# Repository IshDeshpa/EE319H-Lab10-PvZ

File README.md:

# EE319H-Lab10-PvZ
Luke Mason and Ishan Deshpande's EE319H Final Project: Plants vs Zombies

This is a close representation of the real PvZ mobile/console game.

# Game description:
A mob of fun-loving zombies is about to invade your home, and your only defense is an arsenal of 8 zombie-zapping plants. Use peashooters, wall-nuts, cherry bombs and more to mulchify 8 different types of zombies before they can reach your front door.

# Project notes:
The TM4C has 256kB of flash memory (read only for our purposes), and 32kB of SRAM. Additionally, the display, the ST7735R TFT LCD display, was 160x128p, and could support a microSD card of 4GB formatted in FAT16. 

The sprites and sound effects took up almost all 256kB flash, and the in game objects took up almost all of our 32kB SRAM. In total, there were almost 100 sprites, and 7 sound effects. Each plant and zombie had animations with up to 7 sprites. For sound, we used an 8-bit DAC, and the MC34119P amplifier chip, which was paired with a 1MOhm feedback potentiometer, and a high pass filter for sound smoothing.

We implemented the eight starter plants in the game: Sunflower, Peashooter, Potato Mine, Snow Pea, Repeater, Cherry Bomb, Chomper, and Wall-nut. We also implemented eight zombies: regular zombie, conehead, buckethead, polevault, newspaper, jack-in-the-box, football, and flag zombie.

Some of the biggest challenges we ran into involved unrendering the sprites so as to not cause sprite clipping or leftover sprite data upon death. We also had to rewrite the drivers for displaying sprites to be oriented in landscape form.

You can watch our video showcase for our class design competition here: https://www.youtube.com/watch?v=L5PAtDdpwP4
Our game ran rather well with high sprite counts. This can be seen in this additional video, for anyone interested: https://youtu.be/gowIHrNNptc 

Scrapped Features:
- We were intending to implement a VS mode, which was scrapped due to lack of time. 
- We were intending to have music play during the game. However, after extensive debugging of the provided sound drivers, as well as an attempted switch to DMA, we decided that it was not worth our time to combine the display with reading music off of the microSD (Long WAV files are too big to contain in our flash memory, so you have to read it from the display microSD, which detracts from our ability to write SPI to the display's screen)
- We were also intending to seat our diplay and controls on a PCB. Unfortunately, those were lost in delivery, so we threw together a cardboard game controller.

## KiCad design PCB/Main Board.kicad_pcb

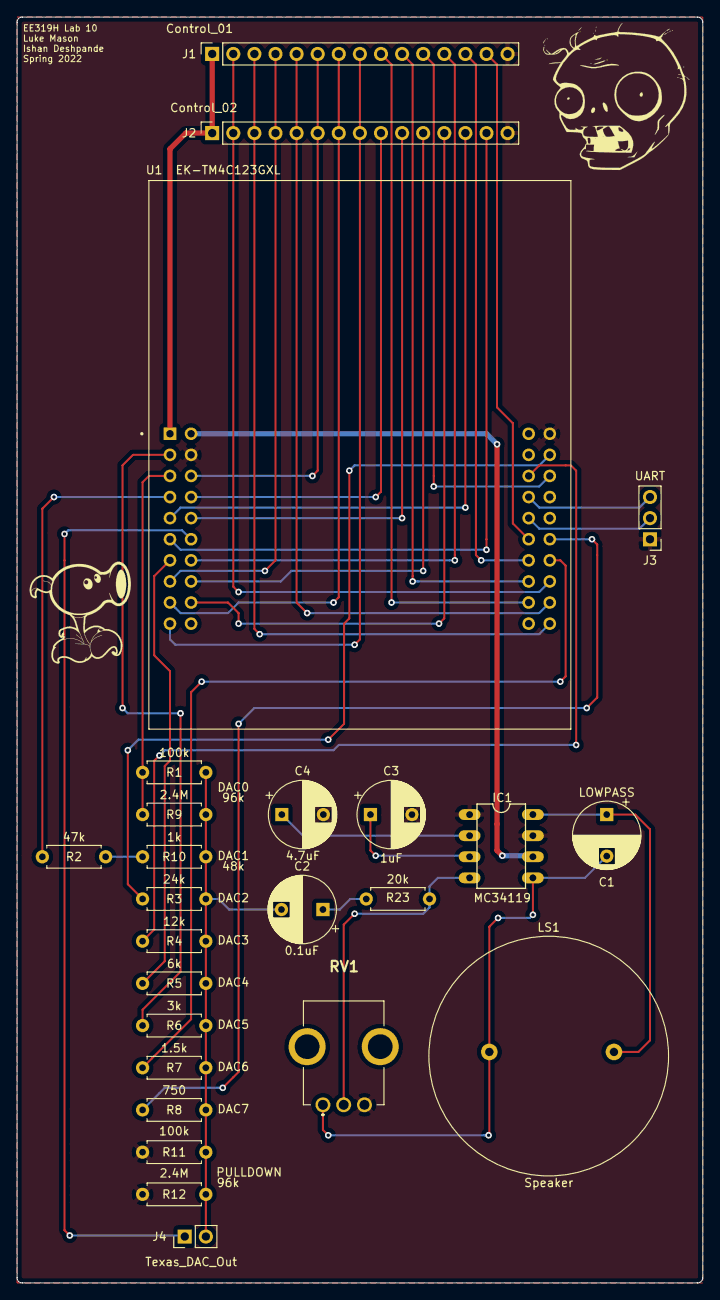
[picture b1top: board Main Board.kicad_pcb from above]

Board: 2 copper layers, 82.5 x 152.4 mm, 25 parts (0 on the bottom side), 41 nets.

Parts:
C1: LOWPASS; CP_Radial_D8.0mm_P5.00mm
C2: 0.1uF; CP_Radial_D8.0mm_P5.00mm
C3: 1uF; CP_Radial_D8.0mm_P5.00mm
C4: 4.7uF; CP_Radial_D8.0mm_P5.00mm
IC1: MC34119; DIL08
J1: Control_01; PinSocket_1x15_P2.54mm_Vertical
J2: Control_02; PinSocket_1x15_P2.54mm_Vertical
J3: UART; PinHeader_1x03_P2.54mm_Vertical
J4: Texas_DAC_Out; PinHeader_1x02_P2.54mm_Vertical
LS1: Speaker; AST-03008MR-R
R1, R11: 100k; R_Axial_DIN0207_L6.3mm_D2.5mm_P7.62mm_Horizontal
R2: 47k; R_Axial_DIN0207_L6.3mm_D2.5mm_P7.62mm_Horizontal
R3: 24k; R_Axial_DIN0207_L6.3mm_D2.5mm_P7.62mm_Horizontal
R4: 12k; R_Axial_DIN0207_L6.3mm_D2.5mm_P7.62mm_Horizontal
R5: 6k; R_Axial_DIN0207_L6.3mm_D2.5mm_P7.62mm_Horizontal
R6: 3k; R_Axial_DIN0207_L6.3mm_D2.5mm_P7.62mm_Horizontal
R7: 1.5k; R_Axial_DIN0207_L6.3mm_D2.5mm_P7.62mm_Horizontal
R8: 750; R_Axial_DIN0207_L6.3mm_D2.5mm_P7.62mm_Horizontal
R9, R12: 2.4M; R_Axial_DIN0207_L6.3mm_D2.5mm_P7.62mm_Horizontal
R10: 1k; R_Axial_DIN0207_L6.3mm_D2.5mm_P7.62mm_Horizontal
R23: 20k; R_Axial_DIN0207_L6.3mm_D2.5mm_P7.62mm_Horizontal
RV1: VOL_POT; PTV09A4020FB103
U1: EK-TM4C123GXL; MODULE_EK-TM4C123GXL

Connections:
+3V3: J1.1, J2.1, U1.J1_1
+5V: IC1.6, U1.J3_1
/A1: J1.9, U1.J4_9
/A2: J2.9, U1.J3_4
/B1: J1.10, U1.J4_8
/B2: J2.10, U1.J3_5
/BL1: J1.13, U1.J4_7
/BL2: J2.13, U1.J1_5
/BR1: J1.14, U1.J4_6
/BR2: J2.14, U1.J1_6
/CARD_CS: J1.6, J2.6, U1.J3_3
/DAC0: R1.2, R9.2, U1.J1_3
/DAC1: R2.2, U1.J1_4
/DAC2: R3.2, U1.J2_2
/DAC3: R4.2, U1.J4_3
/DAC4: R5.2, U1.J1_7
/DAC5: R6.2, U1.J1_2
/DAC6: R7.2, U1.J2_7
/DAC7: R8.2, U1.J2_6
/DACOUT: C2.2, J4.2, R1.1, R3.1, R4.1, R5.1, R6.1, R7.1, R8.1, R9.1, R10.1, R11.2, R12.2
/D_C: J1.7, J2.7, U1.J1_9
/J1_X: J1.11, U1.J2_3
/J1_Y: J1.12, U1.J3_7
/J2_X: J2.11, U1.J3_8
/J2_Y: J2.12, U1.J3_9
/MISO: J1.2, J2.2, U1.J2_8
/MOSI: J1.4, J2.4, U1.J1_8
/RESET: J1.8, J2.8, U1.J1_10
/SCK: J1.3, J2.3, U1.J2_10
/TEXAS: J4.1, U1.J3_6
/TFT_CS: J1.5, J2.5, U1.J2_9
GND: C3.2, C4.2, IC1.1, IC1.7, J1.15, J2.15, J3.1, R11.1, R12.1, RV1.3, U1.J2_1, U1.J3_2
unnamed: C1.1, IC1.8, LS1.2
unnamed: C1.2, IC1.5, LS1.1, RV1.1
unnamed: C2.1, R23.2
unnamed: C3.1, IC1.3
unnamed: C4.1, IC1.2
unnamed: IC1.4, R23.1, RV1.2
unnamed: J3.2, U1.J4_5
unnamed: J3.3, U1.J4_4
unnamed: R2.1, R10.2

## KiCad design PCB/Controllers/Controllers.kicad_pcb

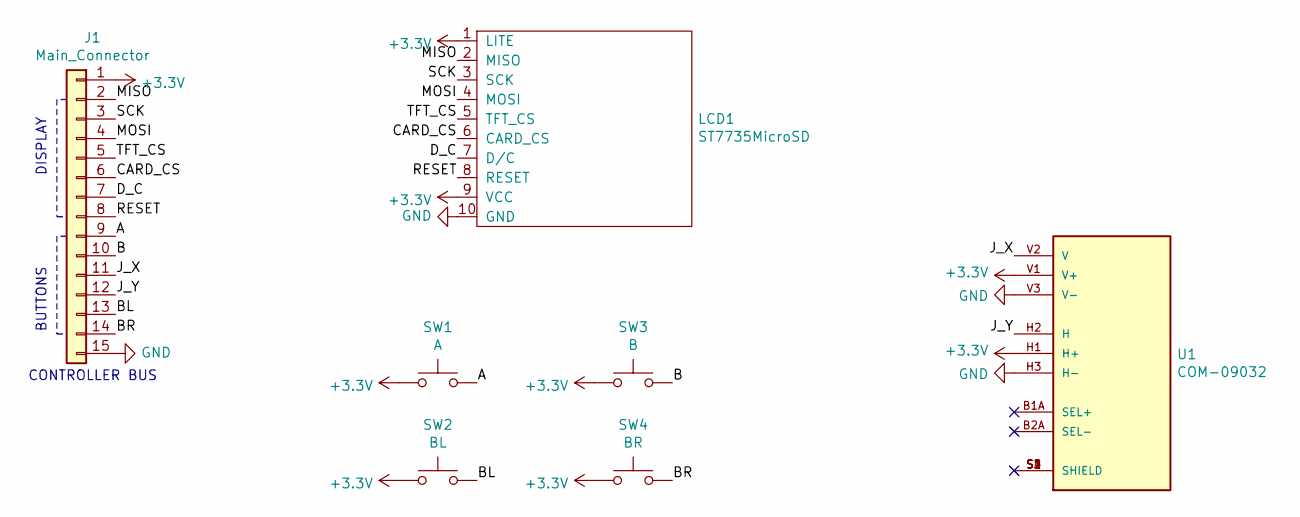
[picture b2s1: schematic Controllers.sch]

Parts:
J1: Main_Connector; PinSocket_1x15_P2.54mm_Horizontal
LCD1: ST7735MicroSD
SW1: A; SW_PUSH-12mm
SW2: BL; SW_PUSH-12mm
SW3: B; SW_PUSH-12mm
SW4: BR; SW_PUSH-12mm
U1: COM-09032; XDCR_COM-09032; PARTREV N/A

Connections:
+3V3: J1.1, LCD1.1 (LITE), LCD1.9 (VCC), SW1.1, SW2.1, SW3.1, SW4.1, U1.H1 (H+), U1.V1 (V+)
/A: J1.9, SW1.2
/B: J1.10, SW3.2
/BL: J1.13, SW2.2
/BR: J1.14, SW4.2
/CARD_CS: J1.6, LCD1.6 (CARD_CS)
/D_C: J1.7, LCD1.7 (D/C)
/J_X: J1.11, U1.V2 (V)
/J_Y: J1.12, U1.H2 (H)
/MISO: J1.2, LCD1.2 (MISO)
/MOSI: J1.4, LCD1.4 (MOSI)
/RESET: J1.8, LCD1.8 (RESET)
/SCK: J1.3, LCD1.3 (SCK)
/TFT_CS: J1.5, LCD1.5 (TFT_CS)
GND: J1.15, LCD1.10 (GND), U1.H3 (H-), U1.V3 (V-)
unnamed: U1.S1 (SHIELD), U1.S2 (SHIELD), U1.S3 (SHIELD), U1.S4 (SHIELD)

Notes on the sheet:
CONTROLLER BUS
BUTTONS
DISPLAY

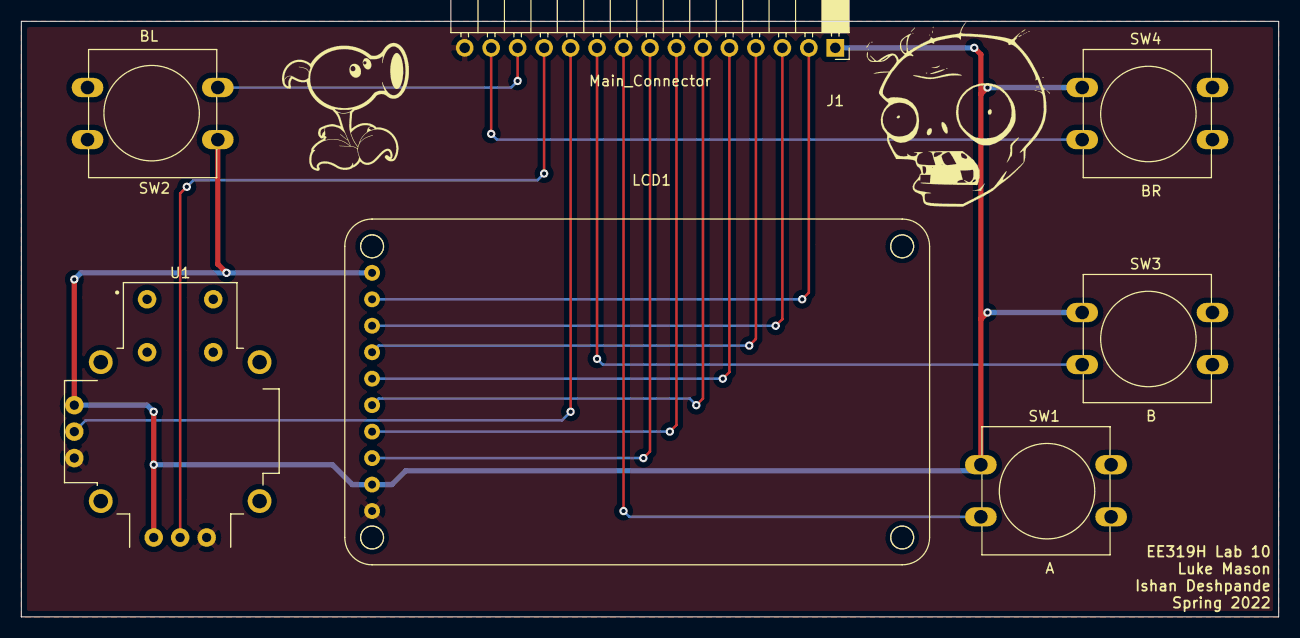
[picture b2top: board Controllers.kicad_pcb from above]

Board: 2 copper layers, 120.7 x 57.1 mm, 7 parts (0 on the bottom side), 16 nets.

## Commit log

2022-04-12 Started setting up game.c
2022-04-13 updated Game.h
2022-04-13 hello
2022-04-13 Added some test comments
2022-04-13 removed
2022-04-13 Added some test comments (#2)
    * Added some test comments
    * removed
2022-04-13 Added entity, projectile, and Plant.h
2022-04-14 plant stuff
2022-04-14 Game and Plant changes
2022-04-14 created zombie.h and some classes
2022-04-14 saved this tiem
2022-04-14 plant changes mostly
2022-04-14 added flag, armor, cone, bucket, football, news, and pole zombie headers and stubs
2022-04-18 finishjed plant and changed game
2022-04-18 added definitions and projextile.h
2022-04-18 ordered controllers and main board, generated gerbers
2022-04-18 generated gerbers and ordered PCB
2022-04-18 generated gerbers and ordered PCB (#9)
2022-04-19 added jack in the box zombie
2022-04-19 plant stuff (#5)
    * plant stuff
    * Game and Plant changes
    * saved this tiem
    * plant changes mostly
    * finishjed plant and changed game
    * added definitions and projextile.h
2022-04-19 Zombie stuff (#6)
    * plant stuff
    * Game and Plant changes
    * created zombie.h and some classes
    * saved this tiem
    * added flag, armor, cone, bucket, football, news, and pole zombie headers and stubs
    * added jack in the box zombie
2022-04-19 added gitignore for keil's stupid files
2022-04-19 remove untracked files
2022-04-20 dac works, notes/music is yet to be working and SD card is yet to be messed with
2022-04-21 dac and music updates
2022-04-21 mostly done with calsses, still need some definitions
2022-04-22 added zombie, lawn, and peashooter assets
2022-04-24 added repeater pngs
2022-04-24 changed some sizing information
2022-04-24 added PD0 support for CS to diskio
2022-04-25 got SDC mostly working, few small bugs (check issue)
2022-04-25 Apply suggestions from code review
2022-04-25 Updated classes, need to start actual code (#13)
    * mostly done with calsses, still need some definitions
    * Apply suggestions from code review
2022-04-26 almost done with music. kind of works but has an annoying beeping sound that i think may be caused by all of the interrupts. going to hook it up to an oscilloscope tomorrow
2022-04-26 fixed buffer size and made global
2022-04-27 partway through
2022-04-27 got main theme working pretty well, reformatted drivers for sd and screen
2022-04-27 started setting up DMA
2022-04-27 moved test of filesystem to different file
2022-04-27 Better ST7735 Drivers and working PvZ music (#15)
    * dac works, notes/music is yet to be working and SD card is yet to be messed with
    * dac and music updates
    * added PD0 support for CS to diskio
    * got SDC mostly working, few small bugs (check issue)
    * almost done with music. kind of works but has an annoying beeping sound that i think may be caused by all of the interrupts. going to hook it up to an oscilloscope tomorrow
    * fixed buffer size and made global
2022-04-28 hopefully this doesn't suck
2022-04-28 Scene initialization, merged files together (#17)
    * partway through
    * hopefully this doesn't suck
2022-04-28 good amount of uDMA initialization
2022-04-29 updated gitignore
2022-04-29 worked on display functions for drawing bitmap in new coordinate system
2022-04-30 zombie/collisions not programmed yet
2022-04-30 render and unrender sprite in working condition
2022-05-01 finnished zombies and collision, still missing a couple features
2022-05-01 remove conflicts
2022-05-01 More programming (#21)
    * zombie/collisions not programmed yet
    * merge with ishan stuff and also in desperate need of assets
    * finnished zombies and collision, still missing a couple features
    * remove conflicts
2022-05-01 testing drawsprite
2022-05-01 Render (#22)
    * worked on display functions for drawing bitmap in new coordinate system
    * render and unrender sprite in working condition
    * updated gitignore
    * testing drawsprite
2022-05-01 fixed build issues
2022-05-01 fixed gitignore
2022-05-01 fixed tracking
2022-05-01 added project files
2022-05-01 render cursor working
2022-05-01 created Inputs.cpp
2022-05-01 music is not wroking
2022-05-01 did more cleanup
2022-05-01 adc working
2022-05-01 Set up ADC and render cursor functions (#24)
    * fixed gitignore
    * render cursor working
    * created Inputs.cpp
    * adc working
    * updated gitignore
    * updated gitignore
2022-05-01 flag zombie, sun, lawnmower
2022-05-02 gitignore
2022-05-02 done prograaming
2022-05-02 done with zombies
2022-05-02 added sounds to folder
2022-05-02 only one gray seed sprite now pog
2022-05-02 fixed explosion rendering
2022-05-02 small changes
2022-05-02 rewrote soundfx driver
2022-05-02 update to gitignore
2022-05-02 removed useless files
2022-05-02 Soundfx (#25)
    * added sounds to folder
    * updated gitignore
    * rewrote soundfx driver
    * update to gitignore
2022-05-02 all sprites in hopefully
2022-05-02 fixed sprites
2022-05-02 jank
2022-05-02 Assets (sprites) (#26)
    * added zombie, lawn, and peashooter assets
    * added repeater pngs
    * changed some sizing information
    * flag zombie, sun, lawnmower
    * done with zombies
    * all sprites in hopefully
2022-05-03 cleaning up Game.cpp, added all assets and started init function
2022-05-03 fixed port initialization
2022-05-03 some heap errors, initialization done tho
2022-05-03 game actually runs now
2022-05-03 buttons not working
2022-05-03 bug fixing
2022-05-03 lawnmowers working
2022-05-04 grid cursor issues
2022-05-04 plants softlock, grid no work, need to set sprites' next pointers
2022-05-04 fixed GORmv maybe
2022-05-04 fixed a bunch of things
2022-05-04 merge
2022-05-04 works
2022-05-04 playable
2022-05-04 tried some stuff
2022-05-04 need explosion fix
2022-05-04 explosion fixed
2022-05-05 bugs may have been fixed some
2022-05-05 works beter now
2022-05-18 Testing cleanup (#27)
    * cleaning up Game.cpp, added all assets and started init function
    * fixed port initialization
    * some heap errors, initialization done tho
    * game actually runs now
    * buttons not working
    * bug fixing
